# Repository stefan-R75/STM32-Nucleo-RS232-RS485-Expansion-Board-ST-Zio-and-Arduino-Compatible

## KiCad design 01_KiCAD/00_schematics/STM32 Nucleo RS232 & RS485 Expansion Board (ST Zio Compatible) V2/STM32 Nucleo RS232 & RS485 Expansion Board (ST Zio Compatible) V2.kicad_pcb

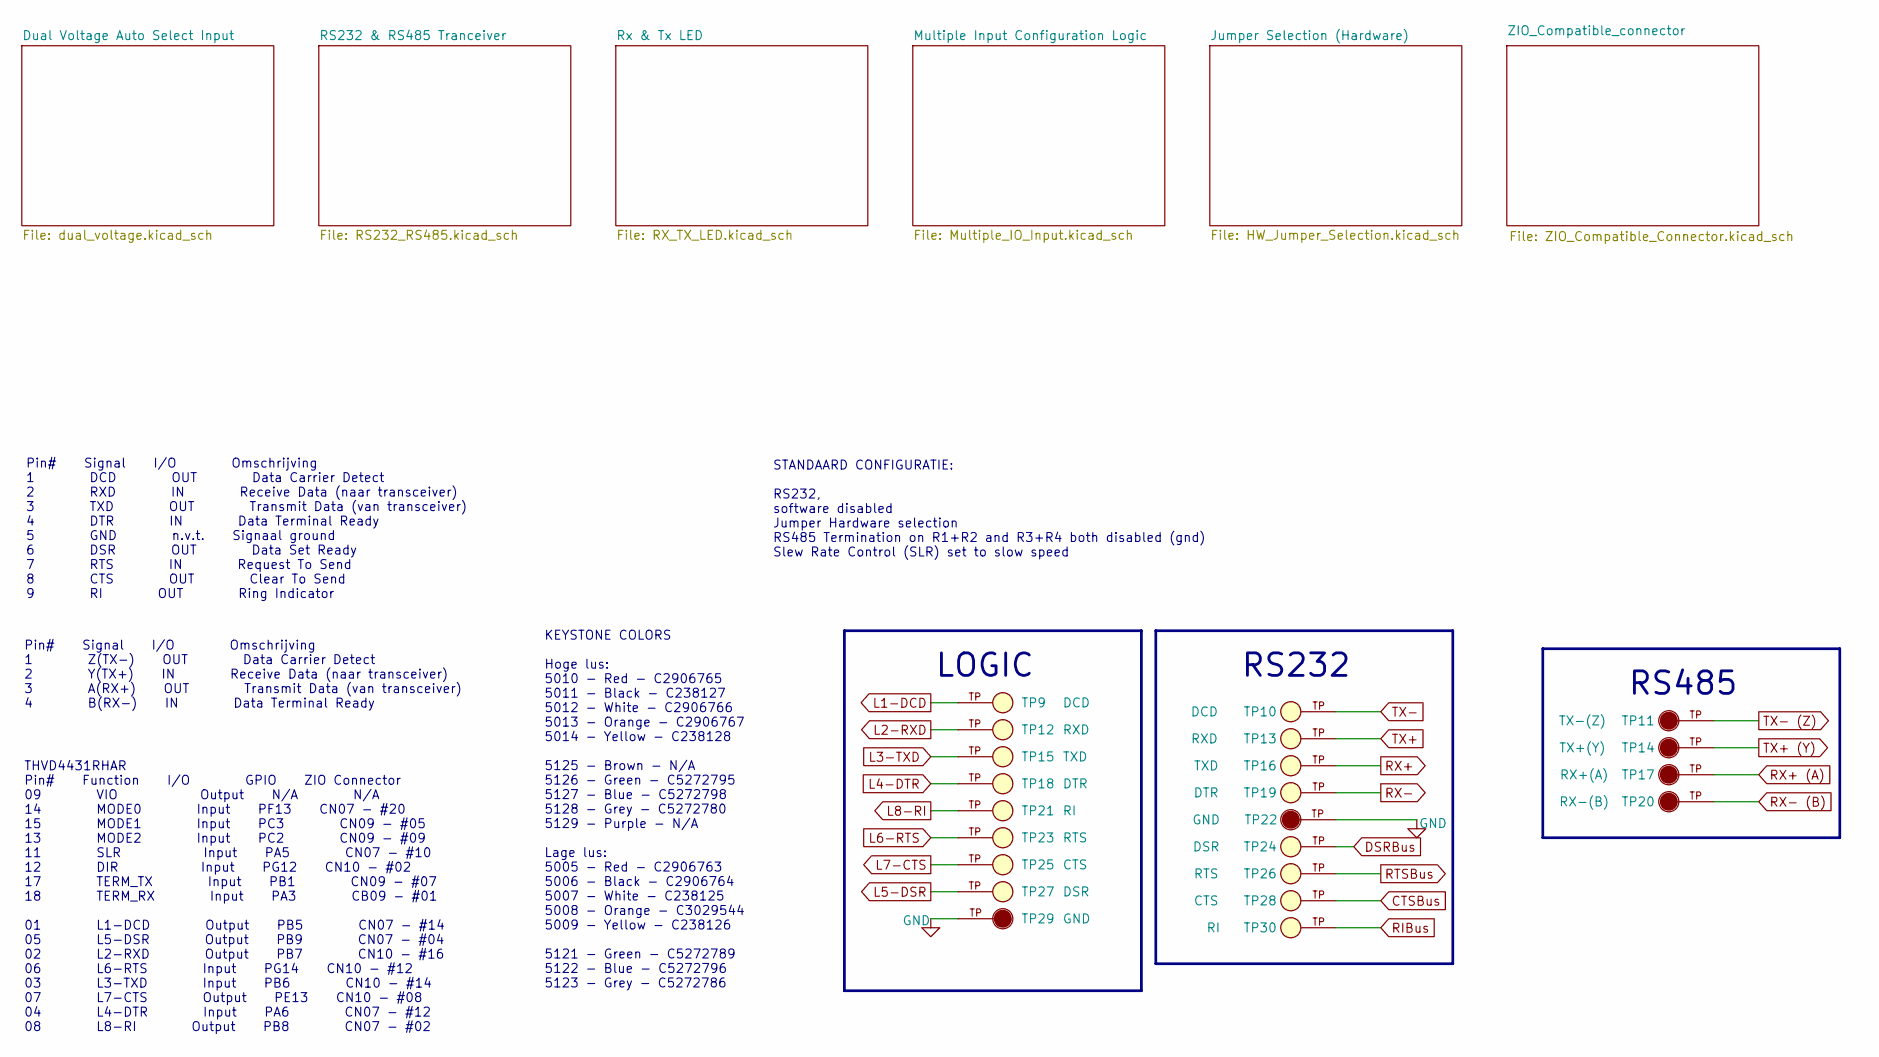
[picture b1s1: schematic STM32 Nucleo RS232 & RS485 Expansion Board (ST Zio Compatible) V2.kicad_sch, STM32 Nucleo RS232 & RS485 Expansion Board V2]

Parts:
TP9, TP10: DCD; KEYSTONE_5121; PARTREV F; LCSC C5272789
TP11: TX-(Z); KEYSTONE_5009; PARTREV F; LCSC C238128
TP12, TP13: RXD; KEYSTONE_5122; PARTREV F; LCSC C5272796
TP14: TX+(Y); KEYSTONE_5009; PARTREV F; LCSC C238128
TP15, TP16: TXD; KEYSTONE_5122; PARTREV F; LCSC C5272796
TP17: RX+(A); KEYSTONE_5008; PARTREV F; LCSC C2906767
TP18, TP19: DTR; KEYSTONE_5121; PARTREV F; LCSC C5272789
TP20: RX-(B); KEYSTONE_5008; PARTREV F; LCSC C2906767
TP21, TP30: RI; KEYSTONE_5121; PARTREV F; LCSC C5272789
TP22, TP29: GND; KEYSTONE_5006; PARTREV F; LCSC C2906764
TP23, TP26: RTS; KEYSTONE_5122; PARTREV F; LCSC C5272796
TP24, TP27: DSR; KEYSTONE_5122; PARTREV F; LCSC C5272796
TP25, TP28: CTS; KEYSTONE_5122; PARTREV F; LCSC C5272796

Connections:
CTSBus: TP28.TP; also elsewhere on the board
DSRBus: TP24.TP; also elsewhere on the board
GND: TP22.TP, TP29.TP; also elsewhere on the board
L1-DCD: TP9.TP; also elsewhere on the board
L2-RXD: TP12.TP; also elsewhere on the board
L3-TXD: TP15.TP; also elsewhere on the board
L4-DTR: TP18.TP; also elsewhere on the board
L5-DSR: TP27.TP; also elsewhere on the board
L6-RTS: TP23.TP; also elsewhere on the board
L7-CTS: TP25.TP; also elsewhere on the board
L8-RI: TP21.TP; also elsewhere on the board
RIBus: TP30.TP; also elsewhere on the board
RTSBus: TP26.TP; also elsewhere on the board
RX+: TP16.TP; also elsewhere on the board
RX+ (A): TP17.TP; also elsewhere on the board
RX-: TP19.TP; also elsewhere on the board
RX- (B): TP20.TP; also elsewhere on the board
TX+: TP13.TP; also elsewhere on the board
TX+ (Y): TP14.TP; also elsewhere on the board
TX-: TP10.TP; also elsewhere on the board
TX- (Z): TP11.TP; also elsewhere on the board

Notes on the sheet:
LOGIC
Pin# Signal I/O Omschrijving 1 DCD OUT Data Carrier Detect 2 RXD IN Receive Data (naar transceiver) 3 TXD OUT Transmit Data (van transceiver) 4 DTR IN Data Terminal Ready 5 GND n.v.t. Signaal ground 6 DSR OUT Data Set Ready 7 RTS IN Request To Send 8 CTS OUT Clear To Send 9 RI OUT Ring Indicator
KEYSTONE COLORS Hoge lus: 5010 - Red - C2906765 5011 - Black - C238127 5012 - White - C2906766 5013 - Orange - C2906767 5014 - Yellow - C238128 5125 - Brown - N/A 5126 - Green - C5272795 5127 - Blue - C5272798 5128 - Grey - C5272780 5129 - Purple - N/A Lage lus: 5005 - Red - C2906763 5006 - Black -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
Pin# Signal I/O Omschrijving 1 Z(TX-) OUT Data Carrier Detect 2 Y(TX+) IN Receive Data (naar transceiver) 3 A(RX+) OUT Transmit Data (van transceiver) 4 B(RX-) IN Data Terminal Ready
THVD4431RHAR Pin# Function I/O GPIO ZIO Connector 09 VIO Output N/A N/A 14 MODE0 Input PF13 CN07 - #20 15 MODE1 Input PC3 CN09 - #05 13 MODE2 Input PC2 CN09 - #09 11 SLR Input PA5 CN07 - #10 12 DIR Input PG12 CN10 - #02 17 TERM_TX Input PB1 CN09 - #07 18 TERM_RX Input PA3 CB09 - #01 01 L1-DCD Outpu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
STANDAARD CONFIGURATIE: RS232, software disabled Jumper Hardware selection RS485 Termination on R1+R2 and R3+R4 both disabled (gnd) Slew Rate Control (SLR) set to slow speed
RS232
RS485

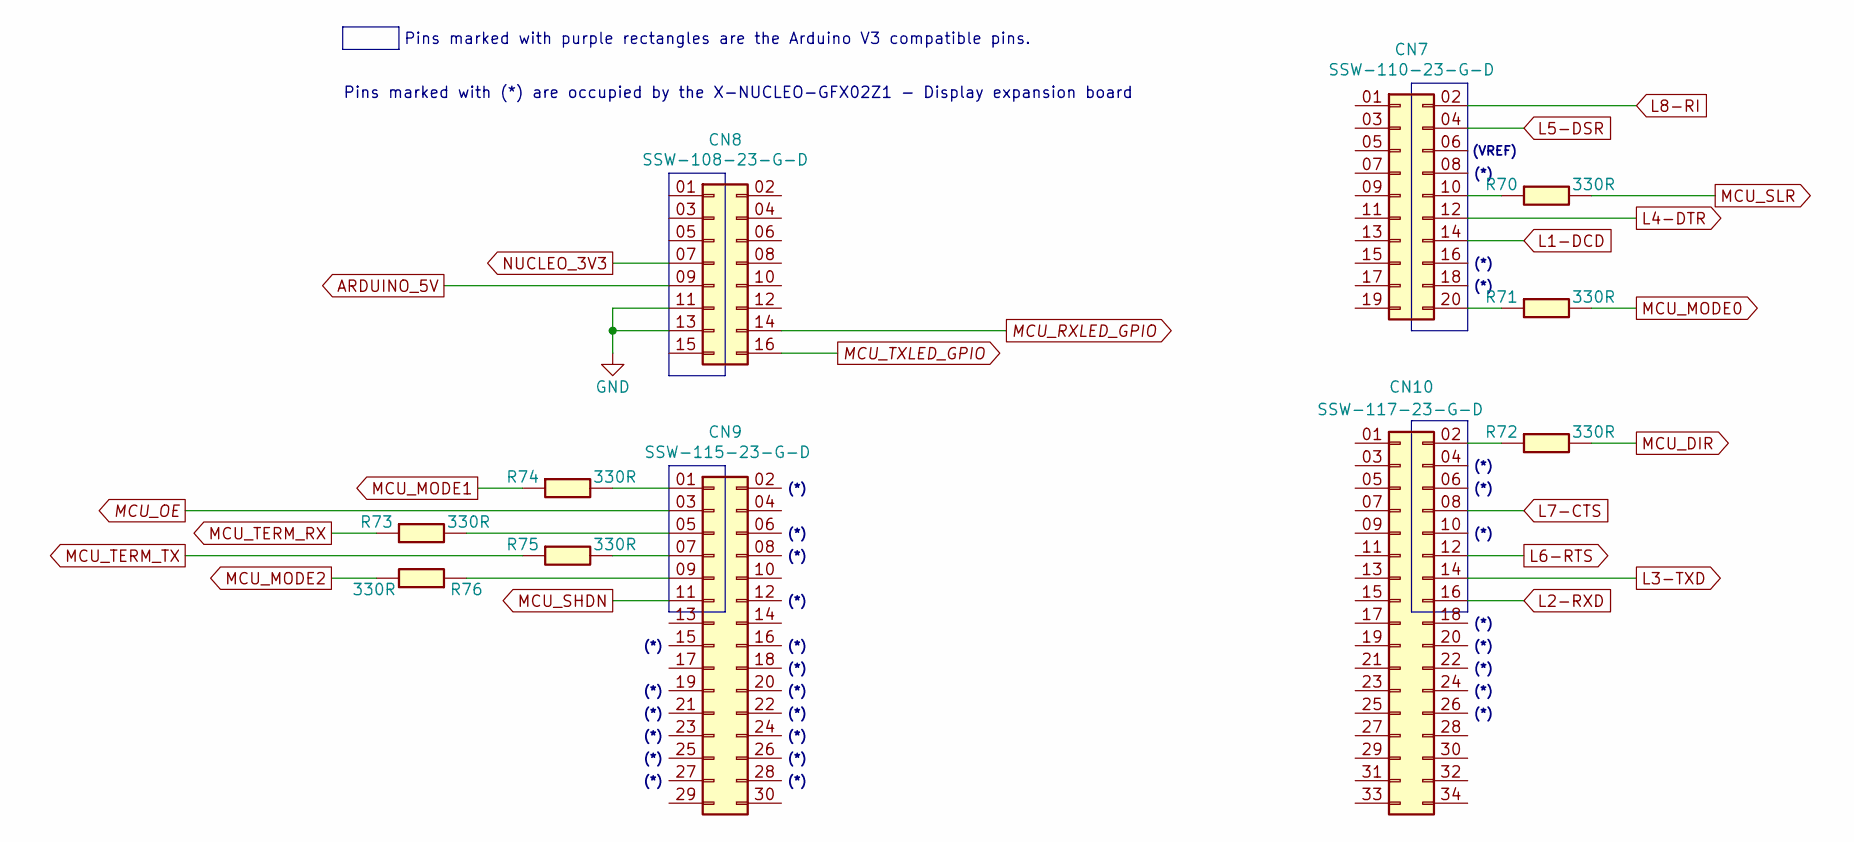
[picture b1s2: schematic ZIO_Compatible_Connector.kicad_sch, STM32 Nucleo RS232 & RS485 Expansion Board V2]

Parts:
CN7: SSW-110-23-G-D; SAMTEC_SSW-110-23-X-D; MPN SSW-110-23-G-D; LCSC C6236460
CN8: SSW-108-23-G-D; SAMTEC_SSW-108-23-F-D; MPN SSW-108-23-G-D; LCSC C7019040
CN9: SSW-115-23-G-D; SAMTEC_SSW-115-23-F-D; MPN SSW-115-23-G-D; LCSC C7089189
CN10: SSW-117-23-G-D; SAMTEC_SSW-117-23-F-D; MPN SSW-117-23-G-D; LCSC C6501751
R70, R71, R72, R73, R74, R75, R76: 330R; R_0603; Voltage Rating 1% 100mW; MPN AC0603FR-7W330RL; LCSC C513549

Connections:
ARDUINO_5V: CN8.09 (Pin_9); also elsewhere on the board
GND: CN8.11, CN8.13; also elsewhere on the board
L1-DCD: CN7.14; also elsewhere on the board
L2-RXD: CN10.16; also elsewhere on the board
L3-TXD: CN10.14; also elsewhere on the board
L4-DTR: CN7.12; also elsewhere on the board
L5-DSR: CN7.04 (Pin_4); also elsewhere on the board
L6-RTS: CN10.12; also elsewhere on the board
L7-CTS: CN10.08 (Pin_8); also elsewhere on the board
L8-RI: CN7.02 (Pin_2); also elsewhere on the board
MCU_DIR: R72.1; also elsewhere on the board
MCU_MODE0: R71.1; also elsewhere on the board
MCU_MODE1: R74.2; also elsewhere on the board
MCU_MODE2: R76.1; also elsewhere on the board
MCU_OE: CN9.03 (Pin_3); also elsewhere on the board
MCU_RXLED_GPIO: CN8.14; also elsewhere on the board
MCU_SHDN: CN9.11; also elsewhere on the board
MCU_SLR: R70.1; also elsewhere on the board
MCU_TERM_RX: R73.2; also elsewhere on the board
MCU_TERM_TX: R75.2; also elsewhere on the board
MCU_TXLED_GPIO: CN8.16; also elsewhere on the board
NUCLEO_3V3: CN8.07 (Pin_7); also elsewhere on the board
unnamed: CN7.10, R70.2
unnamed: CN7.20, R71.2
unnamed: CN9.01 (Pin_1), R74.1
unnamed: CN9.05 (Pin_5), R73.1
unnamed: CN9.07 (Pin_7), R75.1
unnamed: CN9.09 (Pin_9), R76.2
unnamed: CN10.02 (Pin_2), R72.2

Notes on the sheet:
(*)
(VREF)
Pins marked with purple rectangles are the Arduino V3 compatible pins.
Pins marked with (*) are occupied by the X-NUCLEO-GFX02Z1 - Display expansion board

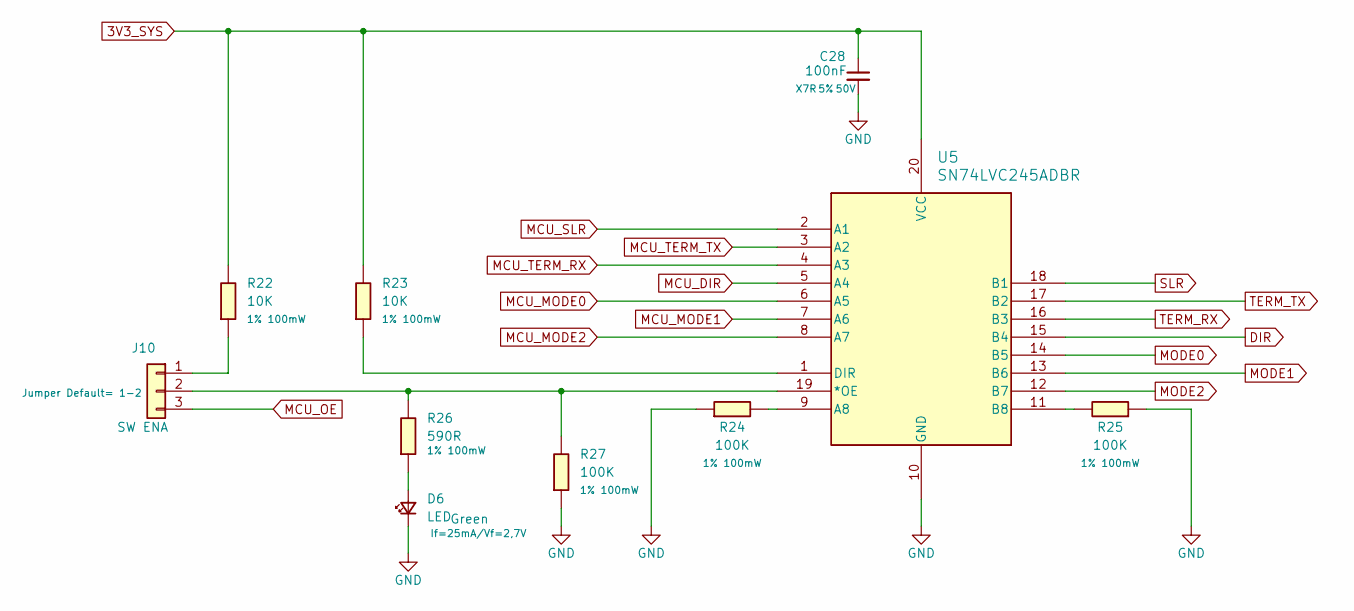
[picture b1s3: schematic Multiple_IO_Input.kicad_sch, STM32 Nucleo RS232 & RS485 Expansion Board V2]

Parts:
C28: 100nF; C_0805_2012Metric; Voltage Rating 50V; Voltage 50V; MPN C0805C104J5RACTU; LCSC C2167095
D6: LED; LED_0603_WRE; Voltage Rating If=25mA/Vf=2,7V; Voltage 2,7V; MPN IN-S63AT5G; LCSC C5656662
J10: SW ENA; Samtec HTSW-103-07-F-S; Voltage Rating Jumper Default= 1-2; MPN HTSW-103-07-F-S; LCSC C5714562
R22, R23: 10K; R_0603; Voltage Rating 1% 100mW; MPN AC0603FR-7W10KL; LCSC C20142011
R24, R25, R27: 100K; R_0603; Voltage Rating 1% 100mW; MPN AC0603FR-7W100KL; LCSC C5552302
R26: 590R; R_0603; Voltage Rating 1% 100mW; MPN AC0603FR-07590RL; LCSC C227973
U5: SN74LVC245ADBR; SOP65P780X200-20N; MPN SN74LVC245ADBR; LCSC C393617

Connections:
3V3_SYS: C28.1, R22.1, R23.1, U5.20 (VCC); also elsewhere on the board
DIR: U5.15 (B4); also elsewhere on the board
GND: C28.2, D6.1 (K), R24.2, R25.2, R27.2, U5.10 (GND); also elsewhere on the board
MCU_DIR: U5.5 (A4); also elsewhere on the board
MCU_MODE0: U5.6 (A5); also elsewhere on the board
MCU_MODE1: U5.7 (A6); also elsewhere on the board
MCU_MODE2: U5.8 (A7); also elsewhere on the board
MCU_OE: J10.3; also elsewhere on the board
MCU_SLR: U5.2 (A1); also elsewhere on the board
MCU_TERM_RX: U5.4 (A3); also elsewhere on the board
MCU_TERM_TX: U5.3 (A2); also elsewhere on the board
MODE0: U5.14 (B5); also elsewhere on the board
MODE1: U5.13 (B6); also elsewhere on the board
MODE2: U5.12 (B7); also elsewhere on the board
unnamed: D6.2 (A), R26.2
unnamed: J10.1, R22.2
unnamed: J10.2, R26.1, R27.1, U5.19 (*OE)
unnamed: R24.1, U5.9 (A8)
unnamed: R25.1, U5.11 (B8)
unnamed: R23.2, U5.1 (DIR)
SLR: U5.18 (B1); also elsewhere on the board
TERM_RX: U5.16 (B3); also elsewhere on the board
TERM_TX: U5.17 (B2); also elsewhere on the board

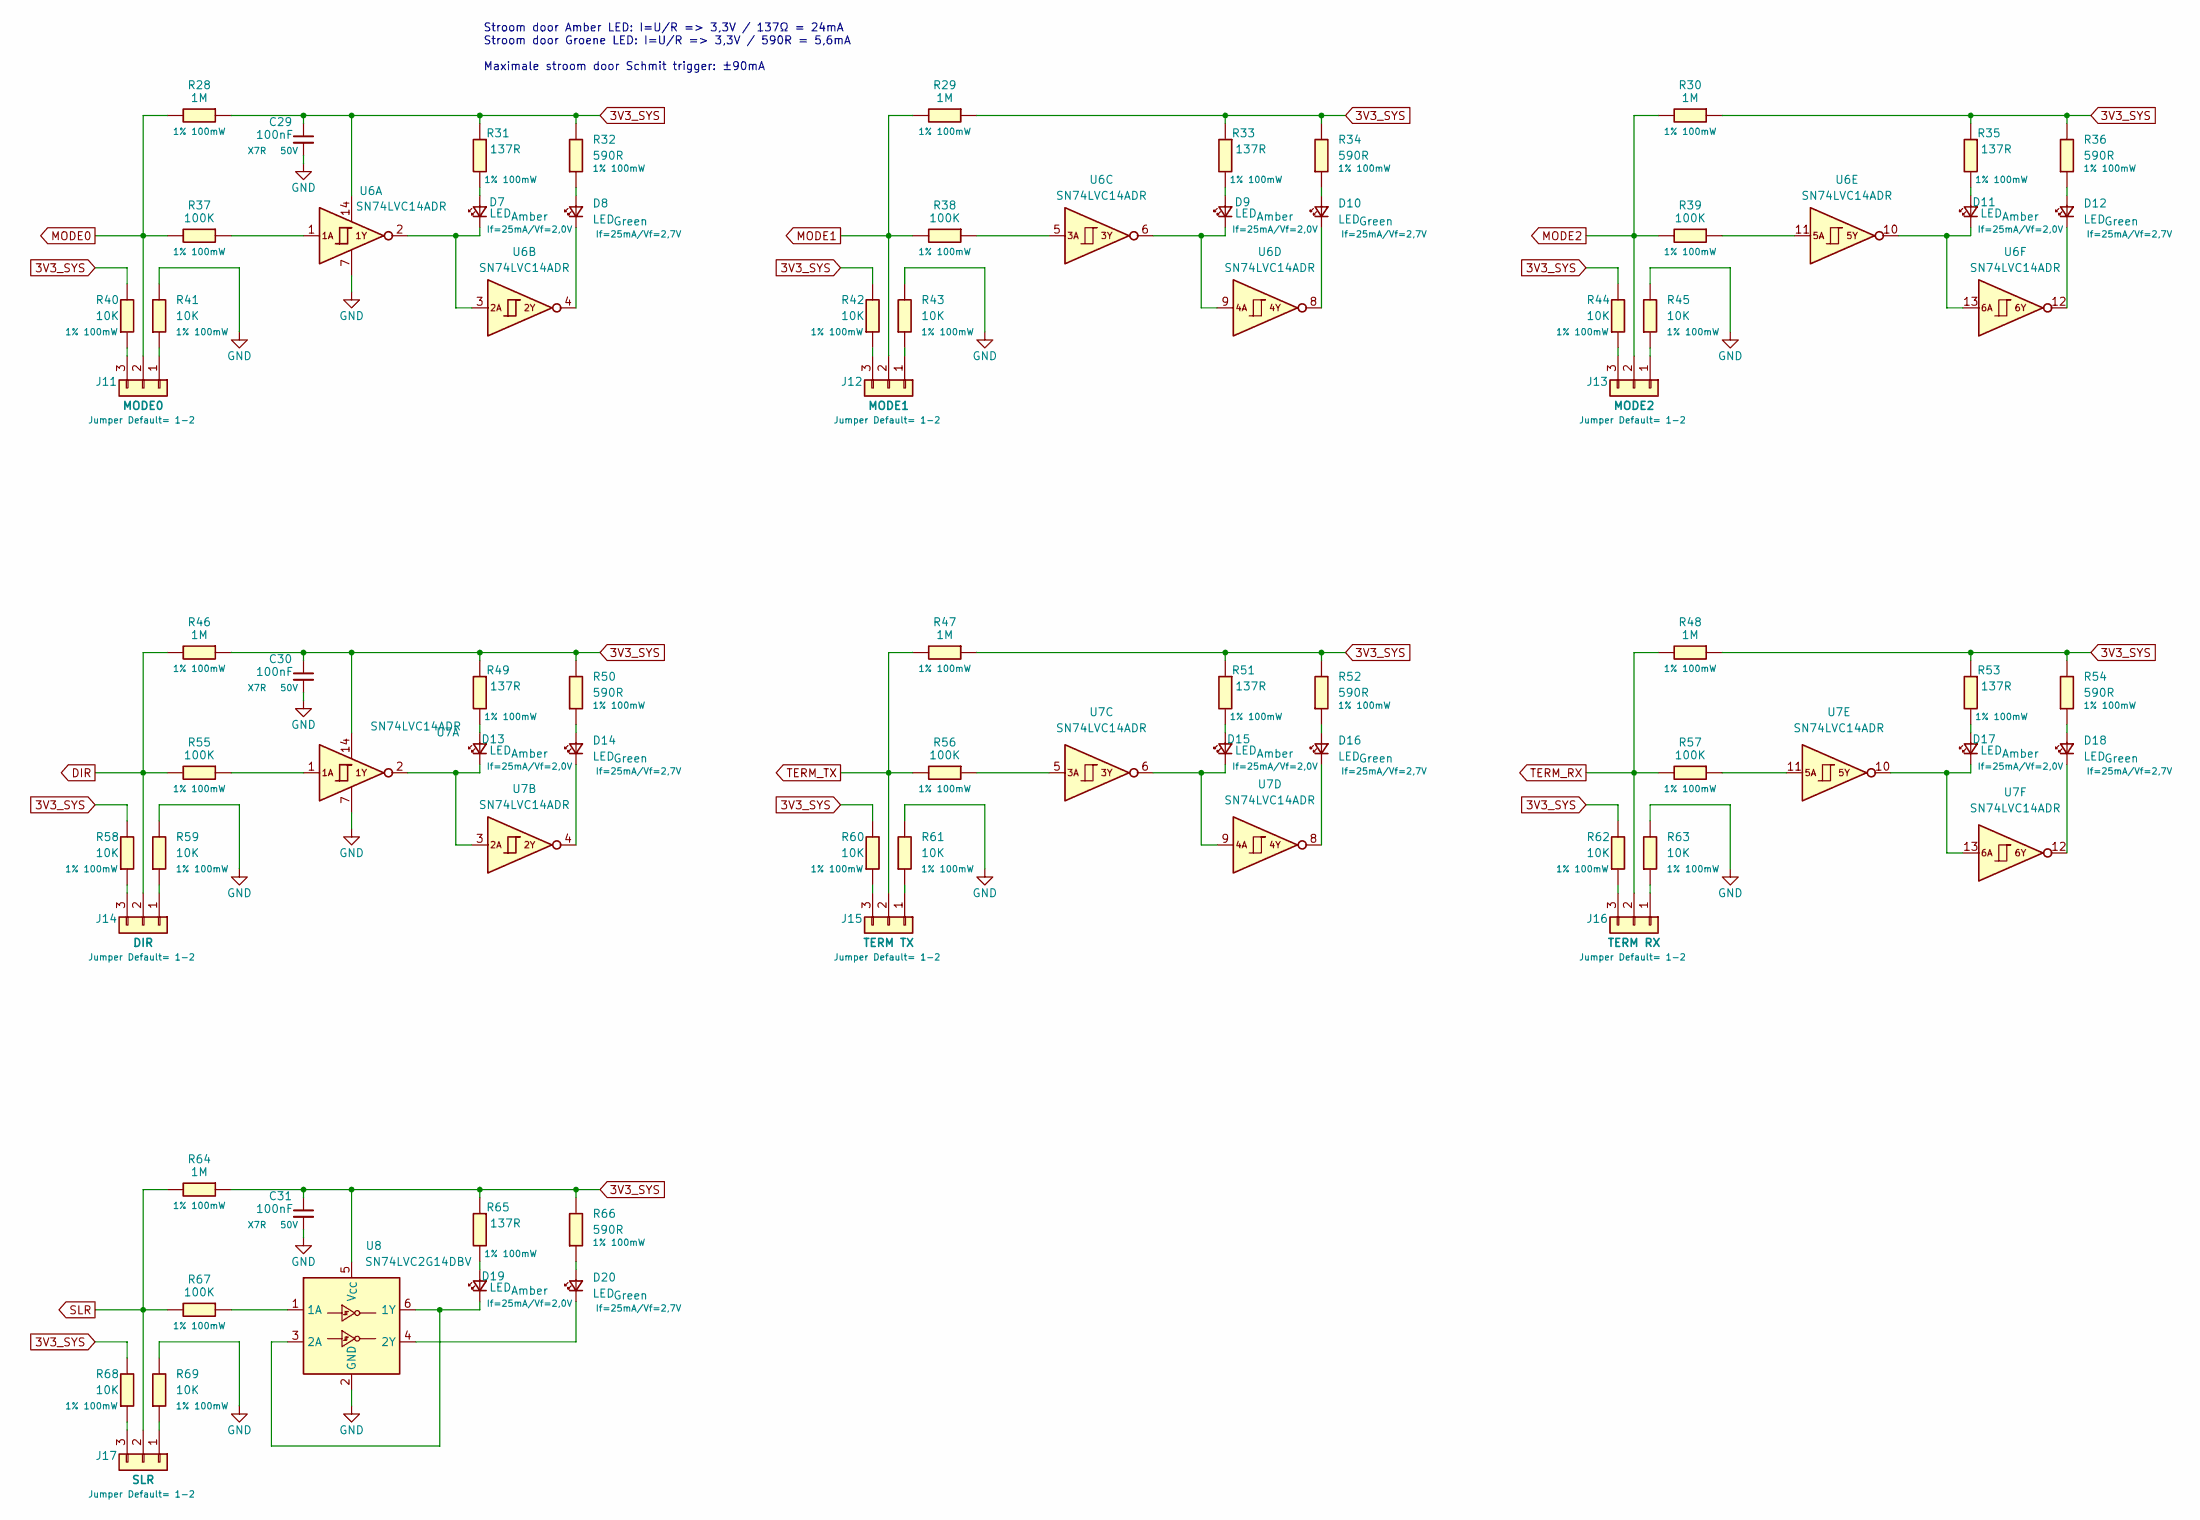
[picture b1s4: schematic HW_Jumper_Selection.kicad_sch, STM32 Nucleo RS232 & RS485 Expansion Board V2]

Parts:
C29, C30, C31: 100nF; C_0805_2012Metric; Voltage Rating 50V; Voltage 50V; MPN C0805C104J5RACTU; LCSC C2167095
D7, D9, D11, D13, D15, D17, D19: LED; LED_0603_WRE; Voltage Rating If=25mA/Vf=2,0V; Voltage 2,0V; MPN IN-S63AT5A; LCSC C5656657
D8, D10, D12, D14, D16, D18, D20: LED; LED_0603_WRE; Voltage Rating If=25mA/Vf=2,7V; Voltage 2,7V; MPN IN-S63AT5G; LCSC C5656662
J11: MODE0; Samtec HTSW-103-07-F-S; Voltage Rating Jumper Default= 1-2; MPN HTSW-103-07-F-S; LCSC C5714562
J12: MODE1; Samtec HTSW-103-07-F-S; Voltage Rating Jumper Default= 1-2; MPN HTSW-103-07-F-S; LCSC C5714562
J13: MODE2; Samtec HTSW-103-07-F-S; Voltage Rating Jumper Default= 1-2; MPN HTSW-103-07-F-S; LCSC C5714562
J14: DIR; Samtec HTSW-103-07-F-S; Voltage Rating Jumper Default= 1-2; MPN HTSW-103-07-F-S; LCSC C5714562
J15: TERM TX; Samtec HTSW-103-07-F-S; Voltage Rating Jumper Default= 1-2; MPN HTSW-103-07-F-S; LCSC C5714562
J16: TERM RX; Samtec HTSW-103-07-F-S; Voltage Rating Jumper Default= 1-2; MPN HTSW-103-07-F-S; LCSC C5714562
J17: SLR; Samtec HTSW-103-07-F-S; Voltage Rating Jumper Default= 1-2; MPN HTSW-103-07-F-S; LCSC C5714562
R28, R29, R30, R46, R47, R48, R64: 1M; R_0603; Voltage Rating 1% 100mW; MPN AC0603FR-7W1ML; LCSC C20142017
R31, R33, R35, R49, R51, R53, R65: 137R; R_0603; Voltage Rating 1% 100mW; MPN AC0603FR-07137KL; LCSC C227579
R32, R34, R36, R50, R52, R54, R66: 590R; R_0603; Voltage Rating 1% 100mW; MPN AC0603FR-07590RL; LCSC C227973
R37, R38, R39, R55, R56, R57, R67: 100K; R_0603; Voltage Rating 1% 100mW; MPN AC0603FR-7W100KL; LCSC C5552302
R40, R41, R42, R43, R44, R45, R58, R59, R60, R61, R62, R63, R68, R69: 10K; R_0603; Voltage Rating 1% 100mW; MPN AC0603FR-7W10KL; LCSC C20142011
U6, U7: SN74LVC14ADR; SOIC127P600X175-14N; MPN SN74LVC14ADR; LCSC C133541
U8: SN74LVC2G14DBV; SOT-23-6; MPN SN74LVC2G14DBVR; LCSC C12401

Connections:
3V3_SYS: C29.1, C30.1, C31.1, R28.2, R29.2, R30.2, R31.2, R32.1, R33.2, R34.1, R35.2, R36.1, R40.1, R42.1, R44.1, R46.2, R47.2, R48.2, R49.2, R50.1, R51.2, R52.1, R53.2, R54.1, R58.1, R60.1, R62.1, R64.2, R65.2, R66.1, R68.1, U6.14 (VCC), U7.14 (VCC), U8.5 (V_{CC}); also elsewhere on the board
DIR: J14.2, R46.1, R55.1; also elsewhere on the board
GND: C29.2, C30.2, C31.2, R41.1, R43.1, R45.1, R59.1, R61.1, R63.1, R69.1, U6.7 (GND), U7.7 (GND), U8.2 (GND); also elsewhere on the board
MODE0: J11.2, R28.1, R37.1; also elsewhere on the board
MODE1: J12.2, R29.1, R38.1; also elsewhere on the board
MODE2: J13.2, R30.1, R39.1; also elsewhere on the board
unnamed: D7.2 (A), R31.1
unnamed: D7.1 (K), U6.2 (1Y), U6.3 (2A)
unnamed: D8.2 (A), R32.2
unnamed: D8.1 (K), U6.4 (2Y)
unnamed: D9.2 (A), R33.1
unnamed: D9.1 (K), U6.6 (3Y), U6.9 (4A)
unnamed: D10.2 (A), R34.2
unnamed: D10.1 (K), U6.8 (4Y)
unnamed: D11.2 (A), R35.1
unnamed: D11.1 (K), U6.10 (5Y), U6.13 (6A)
unnamed: D12.2 (A), R36.2
unnamed: D12.1 (K), U6.12 (6Y)
unnamed: D13.2 (A), R49.1
unnamed: D13.1 (K), U7.2 (1Y), U7.3 (2A)
unnamed: D14.2 (A), R50.2
unnamed: D14.1 (K), U7.4 (2Y)
unnamed: D15.2 (A), R51.1
unnamed: D15.1 (K), U7.6 (3Y), U7.9 (4A)
unnamed: D16.2 (A), R52.2
unnamed: D16.1 (K), U7.8 (4Y)
unnamed: D17.2 (A), R53.1
unnamed: D17.1 (K), U7.10 (5Y), U7.13 (6A)
unnamed: D18.2 (A), R54.2
unnamed: D18.1 (K), U7.12 (6Y)
unnamed: D19.2 (A), R65.1
unnamed: D19.1 (K), U8.3 (2A), U8.6 (1Y)
unnamed: D20.2 (A), R66.2
unnamed: D20.1 (K), U8.4 (2Y)
unnamed: J11.1, R41.2
unnamed: J11.3, R40.2
unnamed: J12.1, R43.2
unnamed: J12.3, R42.2
unnamed: J13.1, R45.2
unnamed: J13.3, R44.2
unnamed: J14.1, R59.2
unnamed: J14.3, R58.2
unnamed: J15.1, R61.2
unnamed: J15.3, R60.2
unnamed: J16.1, R63.2
unnamed: J16.3, R62.2
unnamed: J17.1, R69.2
unnamed: J17.3, R68.2
unnamed: R37.2, U6.1 (1A)
unnamed: R38.2, U6.5 (3A)
unnamed: R39.2, U6.11 (5A)
unnamed: R55.2, U7.1 (1A)
unnamed: R56.2, U7.5 (3A)
unnamed: R57.2, U7.11 (5A)
unnamed: R67.2, U8.1 (1A)
SLR: J17.2, R64.1, R67.1; also elsewhere on the board
TERM_RX: J16.2, R48.1, R57.1; also elsewhere on the board
TERM_TX: J15.2, R47.1, R56.1; also elsewhere on the board

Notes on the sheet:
Stroom door Amber LED: I=U/R => 3,3V / 137Ω = 24mA Stroom door Groene LED: I=U/R => 3,3V / 590R = 5,6mA Maximale stroom door Schmit trigger: ±90mA

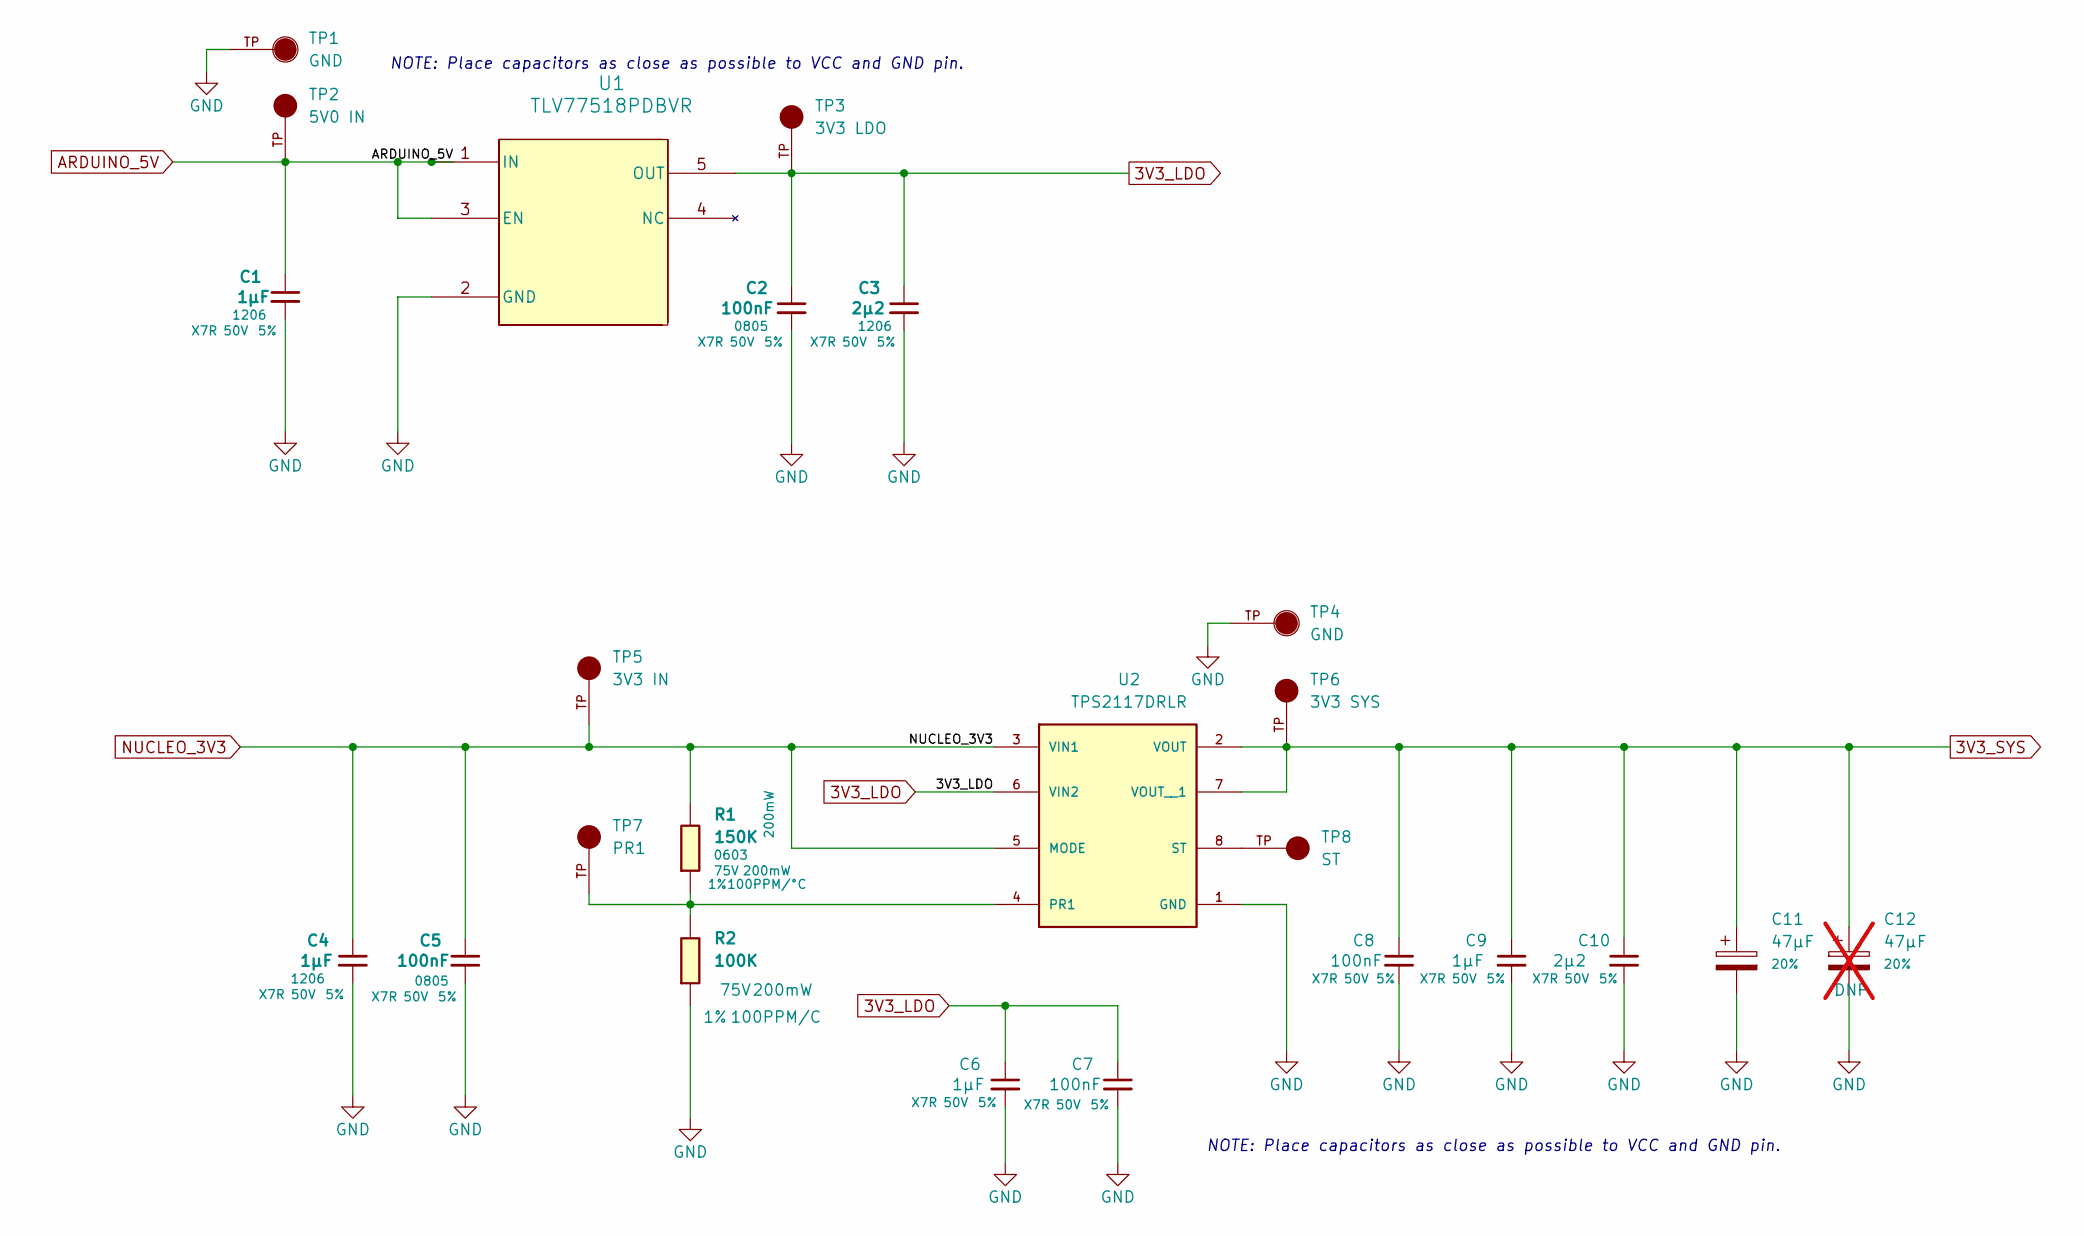
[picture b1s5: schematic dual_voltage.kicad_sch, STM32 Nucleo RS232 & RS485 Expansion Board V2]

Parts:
C1, C4, C6, C9: 1µF; C_1206_3216Metric; Voltage 50V; Tolerance 5%; MPN 12065C105JAT2A; LCSC C597503
C2, C5, C8: 100nF; C_0805_2012Metric; Voltage 50V; Tolerance 5%; MPN C0805C104J5RACTU; LCSC C2167095
C3, C10: 2µ2; C_1206_3216Metric; Voltage 50V; Tolerance 5%; MPN C1206C225J5RECAUTO; LCSC C1513220
C7: 100nF; C_0805_2012Metric; Voltage Rating 50V; Voltage 50V; MPN C0805C104J5RACTU; LCSC C2167095
C11: 47µF; CAP_EEEFT1H470AP; Voltage Rating 50V; Tolerance 20%; MPN EEEFT1H470AP; LCSC C92059
C12: 47µF; CAP_EEEFT1H470AP; Voltage Rating 50V; Tolerance 20%; MPN EEEFT1H470AP; LCSC C92059; not fitted
R1: 150K; R_0603; Voltage 75V; Tolerance 1%; MPN AC0603FR-7W150KL; LCSC C20142013
R2: 100K; R_0603; Voltage 75V; Tolerance 1%; MPN AC0603FR-7W100KL; LCSC C5552302
TP1, TP4: GND; KEYSTONE_5006; PARTREV F; LCSC C2906764
TP2: 5V0 IN; KEYSTONE_5005; PARTREV F; LCSC C2906763
TP3: 3V3 LDO; KEYSTONE_5005; PARTREV F; LCSC C2906763
TP5: 3V3 IN; KEYSTONE_5005; PARTREV F; LCSC C2906763
TP6: 3V3 SYS; KEYSTONE_5005; PARTREV F; LCSC C2906763
TP7: PR1; KEYSTONE_5005; PARTREV F; LCSC C2906763
TP8: ST; KEYSTONE_5005; PARTREV F; LCSC C2906763
U1: TLV77518PDBVR; SOT-23-5_1P75X3P05_TEX; MPN TLV77518PDBVR; LCSC C49292340
U2: TPS2117DRLR; SOTFL50P160X60-8N; PARTREV A; LCSC C22399676

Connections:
3V3_LDO: C2.1, C3.1, C6.1, C7.1, TP3.TP, U1.5 (OUT), U2.6 (VIN2)
3V3_SYS: C8.1, C9.1, C10.1, C11.1, C12.1, TP6.TP, U2.2 (VOUT), U2.7 (VOUT__1); also elsewhere on the board
ARDUINO_5V: C1.1, TP2.TP, U1.1 (IN), U1.3 (EN); also elsewhere on the board
GND: C1.2, C2.2, C3.2, C4.2, C5.2, C6.2, C7.2, C8.2, C9.2, C10.2, C11.2, C12.2, R2.2, TP1.TP, TP4.TP, U1.2 (GND), U2.1 (GND); also elsewhere on the board
NUCLEO_3V3: C4.1, C5.1, R1.1, TP5.TP, U2.3 (VIN1), U2.5 (MODE); also elsewhere on the board
unnamed: R1.2, R2.1, TP7.TP, U2.4 (PR1)
unnamed: TP8.TP, U2.8 (ST)

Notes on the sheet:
NOTE: Place capacitors as close as possible to VCC and GND pin.

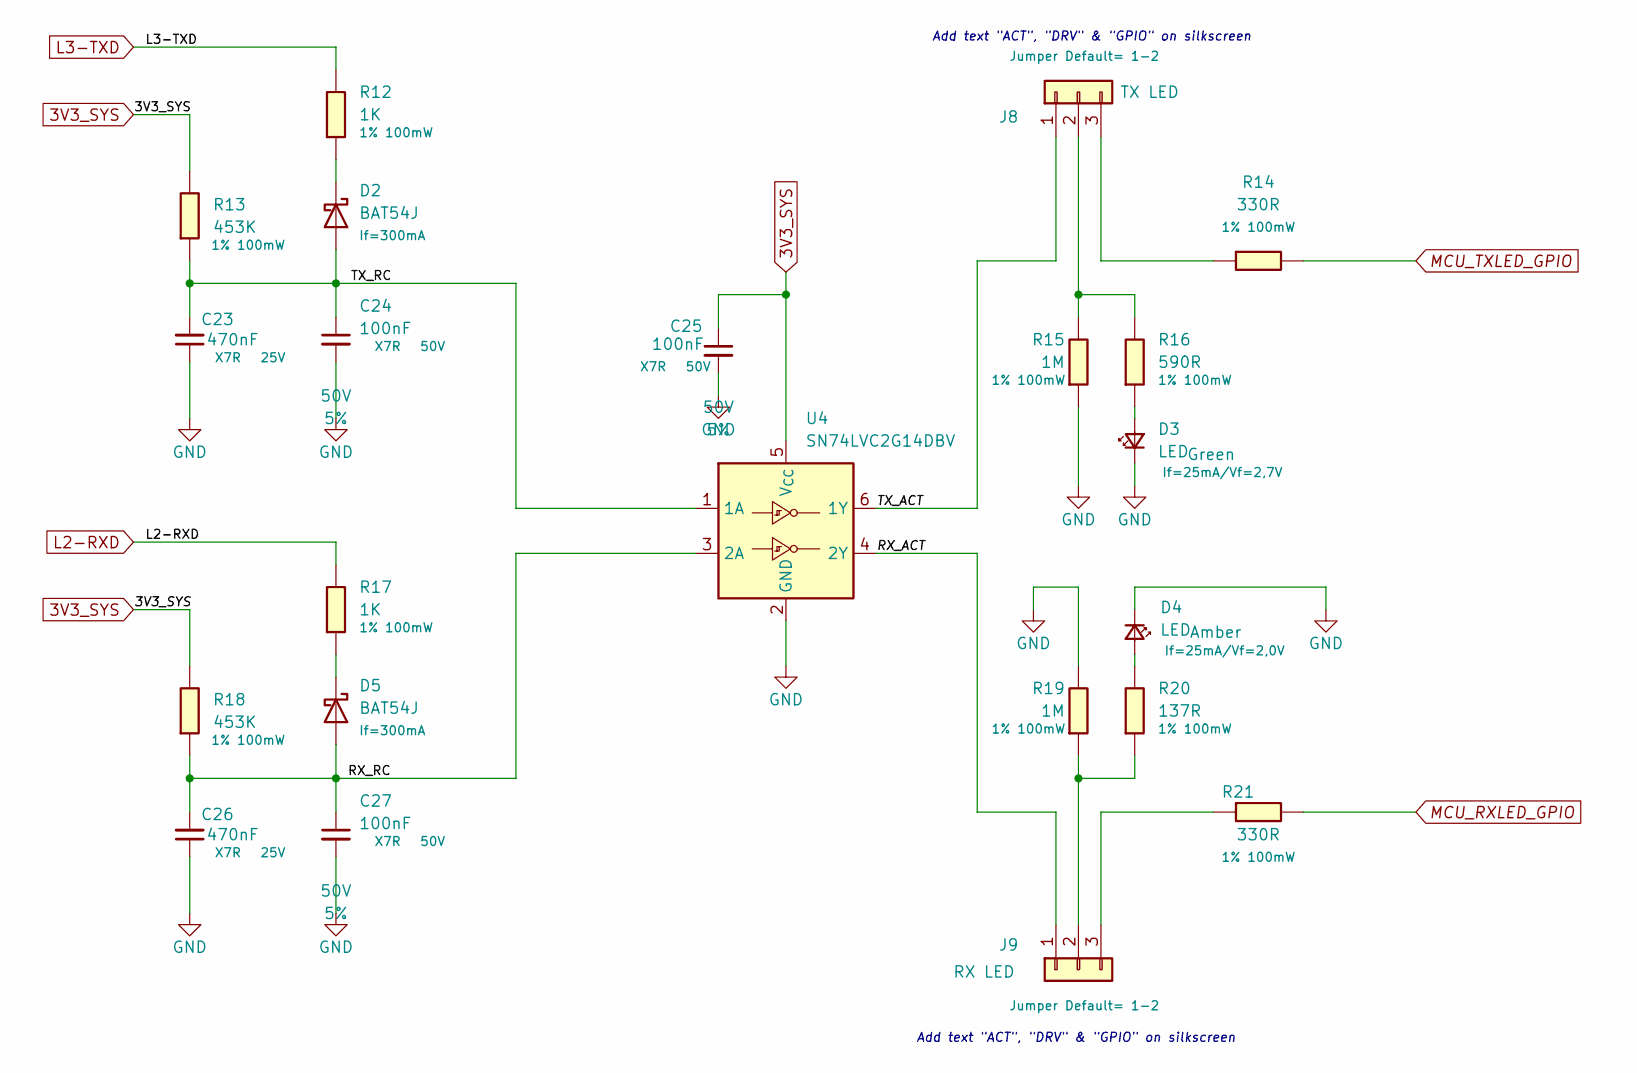
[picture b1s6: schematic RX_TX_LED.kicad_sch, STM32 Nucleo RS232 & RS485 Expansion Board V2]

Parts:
C23, C26: 470nF; C_0805_2012Metric; Voltage Rating 25V; Voltage 50V; MPN 08055C474JAT2A; LCSC C14663
C24, C25, C27: 100nF; C_0805_2012Metric; Voltage Rating 50V; Voltage 50V; MPN C0805C104J5RACTU; LCSC C2167095
D2, D5: BAT54J; D_SOD-323F; Voltage Rating If=300mA; Voltage 40V; MPN BAT54JFILM; LCSC C86299
D3: LED; LED_0603_WRE; Voltage Rating If=25mA/Vf=2,7V; Voltage 2,7V; MPN IN-S63AT5G; LCSC C5656662
D4: LED; LED_0603_WRE; Voltage Rating If=25mA/Vf=2,0V; Voltage 2,0V; MPN IN-S63AT5A; LCSC C5656657
J8: TX LED; Samtec HTSW-103-07-F-S; Voltage Rating Jumper Default= 1-2; MPN HTSW-103-07-F-S; LCSC C5714562
J9: RX LED; Samtec HTSW-103-07-F-S; Voltage Rating Jumper Default= 1-2; MPN HTSW-103-07-F-S; LCSC C5714562
R12, R17: 1K; R_0603; Voltage Rating 1% 100mW; MPN AC0603FR-7W1KL; LCSC C6113732
R13, R18: 453K; R_0603; Voltage Rating 1% 100mW; MPN AC0603FR-07453KL; LCSC C227908
R14, R21: 330R; R_0603; Voltage Rating 1% 100mW; MPN AC0603FR-7W330RL; LCSC C513549
R15, R19: 1M; R_0603; Voltage Rating 1% 100mW; MPN AC0603FR-7W1ML; LCSC C20142017
R16: 590R; R_0603; Voltage Rating 1% 100mW; MPN AC0603FR-07590RL; LCSC C227973
R20: 137R; R_0603; Voltage Rating 1% 100mW; MPN AC0603FR-07137KL; LCSC C227579
U4: SN74LVC2G14DBV; SOT-23-6; MPN SN74LVC2G14DBVR; LCSC C12401

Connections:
3V3_SYS: C25.1, R13.1, R18.1, U4.5 (V_{CC}); also elsewhere on the board
/Rx & Tx LED/RX_ACT: J9.1, U4.4 (2Y)
/Rx & Tx LED/RX_RC: C26.2, C27.1, D5.2 (A), R18.2, U4.3 (2A)
/Rx & Tx LED/TX_ACT: J8.1, U4.6 (1Y)
/Rx & Tx LED/TX_RC: C23.2, C24.1, D2.2 (A), R13.2, U4.1 (1A)
GND: C23.1, C24.2, C25.2, C26.1, C27.2, D3.1 (K), D4.1 (K), R15.2, R19.1, U4.2 (GND); also elsewhere on the board
L2-RXD: R17.1; also elsewhere on the board
L3-TXD: R12.1; also elsewhere on the board
MCU_RXLED_GPIO: R21.1; also elsewhere on the board
MCU_TXLED_GPIO: R14.1; also elsewhere on the board
unnamed: D2.1 (K), R12.2
unnamed: D3.2 (A), R16.2
unnamed: D4.2 (A), R20.1
unnamed: D5.1 (K), R17.2
unnamed: J8.2, R15.1, R16.1
unnamed: J8.3, R14.2
unnamed: J9.2, R19.2, R20.2
unnamed: J9.3, R21.2

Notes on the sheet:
Add text "ACT", "DRV" & "GPIO" on silkscreen

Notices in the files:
01_KiCAD/00_schematics/STM32 Nucleo RS232 & RS485 Expansion Board (ST Zio Compatible) V2/HW_Jumper_Selection.kicad_sch:
Licensed under GNU GPL v3.0 or later
